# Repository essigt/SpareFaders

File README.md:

# SpareFaders

A (still work in progress) STM32-BluePill based MA-Style midi controller featuring 60 buttons and 15 faders.

## PCB

The project is made up of two PCB types. A controller PCB and a keys PCB with can be assambled both for the keys above or under the faders.

### Assembly

## Front Plate

The files for the front plate will be uploaded soon.

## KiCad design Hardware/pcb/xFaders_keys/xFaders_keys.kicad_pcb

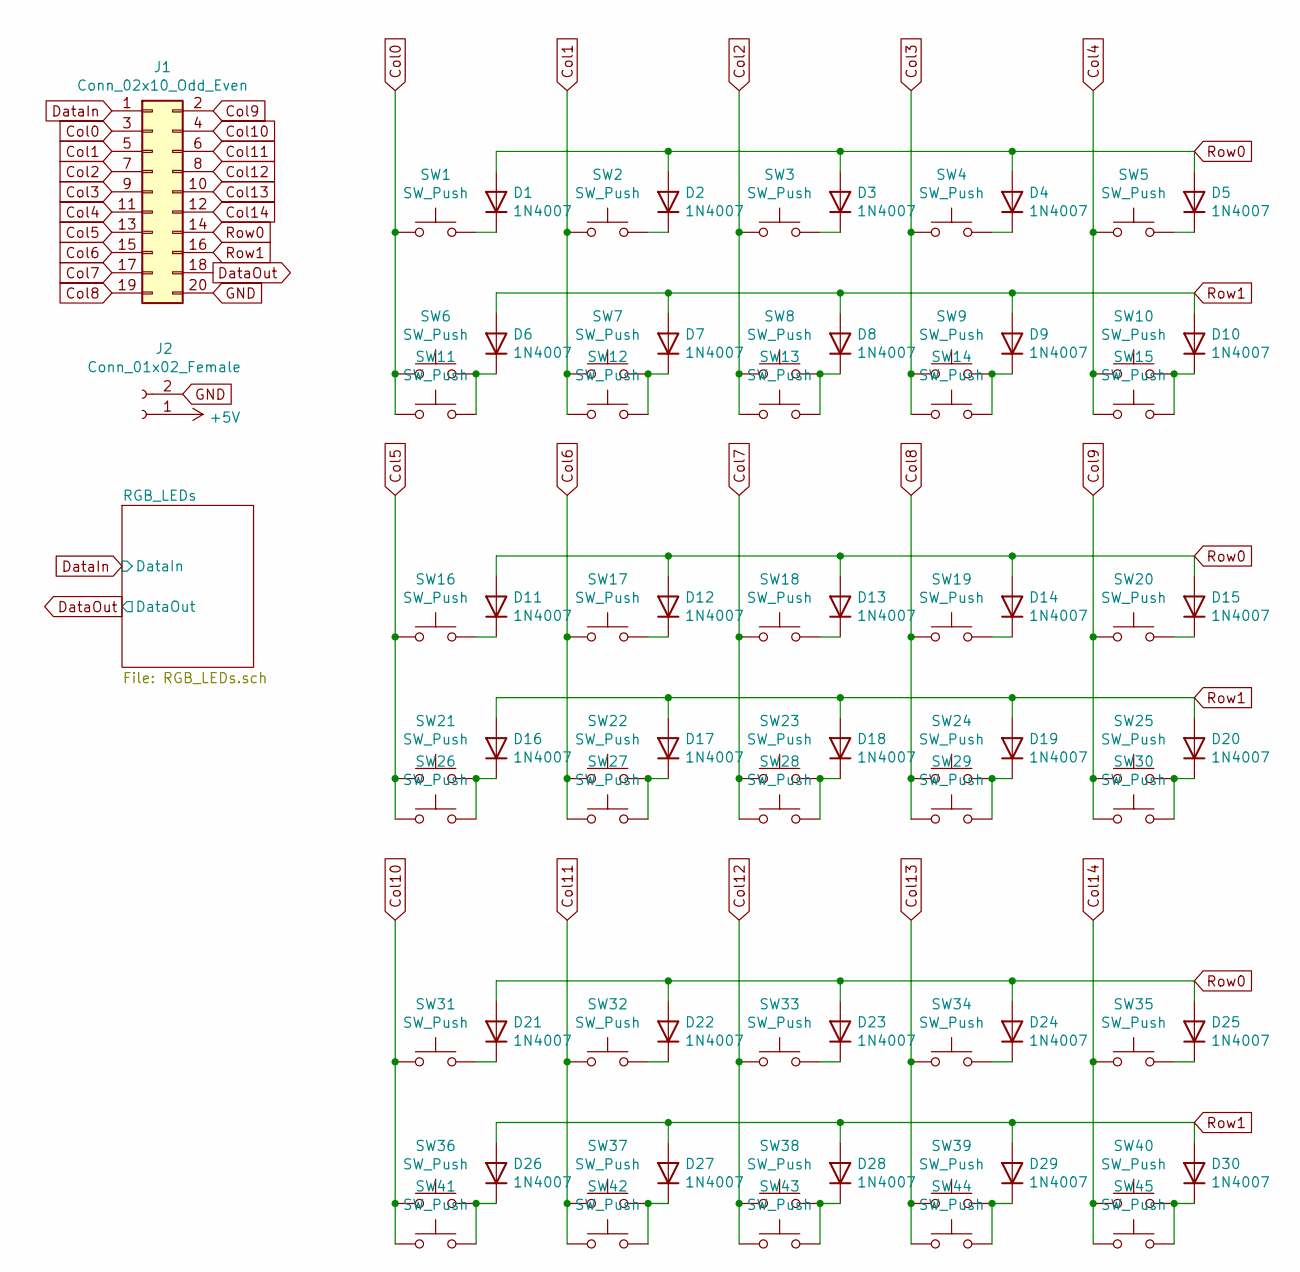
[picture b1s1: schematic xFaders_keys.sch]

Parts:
D1, D2, D3, D4, D5, D6, D7, D8, D9, D10, D11, D12, D13, D14, D15, D16, D17, D18, D19, D20, D21, D22, D23, D24, D25, D26, D27, D28, D29, D30: 1N4007; D_DO-35_SOD27_P10.16mm_Horizontal
J1: Conn_02x10_Odd_Even; PinHeader_2x10_P2.54mm_Vertical
J2: Conn_01x02_Female; PinHeader_1x02_P2.54mm_Vertical
SW1, SW2, SW3, SW4, SW5, SW6, SW7, SW8, SW9, SW10, SW11, SW12, SW13, SW14, SW15, SW16, SW17, SW18, SW19, SW20, SW21, SW22, SW23, SW24, SW25, SW26, SW27, SW28, SW29, SW30, SW31, SW32, SW33, SW34, SW35, SW36, SW37, SW38, SW39, SW40, SW41, SW42, SW43, SW44, SW45: SW_Push; SW_Cherry_MX_1.00u_PCB

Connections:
Col0: J1.3, SW1.1, SW6.1, SW11.1
Col1: J1.5, SW2.1, SW7.1, SW12.1
Col2: J1.7, SW3.1, SW8.1, SW13.1
Col3: J1.9, SW4.1, SW9.1, SW14.1
Col4: J1.11, SW5.1, SW10.1, SW15.1
Col5: J1.13, SW16.1, SW21.1, SW26.1
Col6: J1.15, SW17.1, SW22.1, SW27.1
Col7: J1.17, SW18.1, SW23.1, SW28.1
Col8: J1.19, SW19.1, SW24.1, SW29.1
Col9: J1.2, SW20.1, SW25.1, SW30.1
Col10: J1.4, SW31.1, SW36.1, SW41.1
Col11: J1.6, SW32.1, SW37.1, SW42.1
Col12: J1.8, SW33.1, SW38.1, SW43.1
Col13: J1.10, SW34.1, SW39.1, SW44.1
Col14: J1.12, SW35.1, SW40.1, SW45.1
DataIn: J1.1; also elsewhere on the board
DataOut: J1.18; also elsewhere on the board
unnamed: D1.1 (K), SW1.2
unnamed: D2.1 (K), SW2.2
unnamed: D3.1 (K), SW3.2
unnamed: D4.1 (K), SW4.2
unnamed: D5.1 (K), SW5.2
unnamed: D6.1 (K), SW6.2, SW11.2
unnamed: D7.1 (K), SW7.2, SW12.2
unnamed: D8.1 (K), SW8.2, SW13.2
unnamed: D9.1 (K), SW9.2, SW14.2
unnamed: D10.1 (K), SW10.2, SW15.2
unnamed: D11.1 (K), SW16.2
unnamed: D12.1 (K), SW17.2
unnamed: D13.1 (K), SW18.2
unnamed: D14.1 (K), SW19.2
unnamed: D15.1 (K), SW20.2
unnamed: D16.1 (K), SW21.2, SW26.2
unnamed: D17.1 (K), SW22.2, SW27.2
unnamed: D18.1 (K), SW23.2, SW28.2
unnamed: D19.1 (K), SW24.2, SW29.2
unnamed: D20.1 (K), SW25.2, SW30.2
unnamed: D21.1 (K), SW31.2
unnamed: D22.1 (K), SW32.2
unnamed: D23.1 (K), SW33.2
unnamed: D24.1 (K), SW34.2
unnamed: D25.1 (K), SW35.2
unnamed: D26.1 (K), SW36.2, SW41.2
unnamed: D27.1 (K), SW37.2, SW42.2
unnamed: D28.1 (K), SW38.2, SW43.2
unnamed: D29.1 (K), SW39.2, SW44.2
unnamed: D30.1 (K), SW40.2, SW45.2
Row0: D1.2 (A), D2.2 (A), D3.2 (A), D4.2 (A), D5.2 (A), D11.2 (A), D12.2 (A), D13.2 (A), D14.2 (A), D15.2 (A), D21.2 (A), D22.2 (A), D23.2 (A), D24.2 (A), D25.2 (A), J1.14
Row1: D6.2 (A), D7.2 (A), D8.2 (A), D9.2 (A), D10.2 (A), D16.2 (A), D17.2 (A), D18.2 (A), D19.2 (A), D20.2 (A), D26.2 (A), D27.2 (A), D28.2 (A), D29.2 (A), D30.2 (A), J1.16

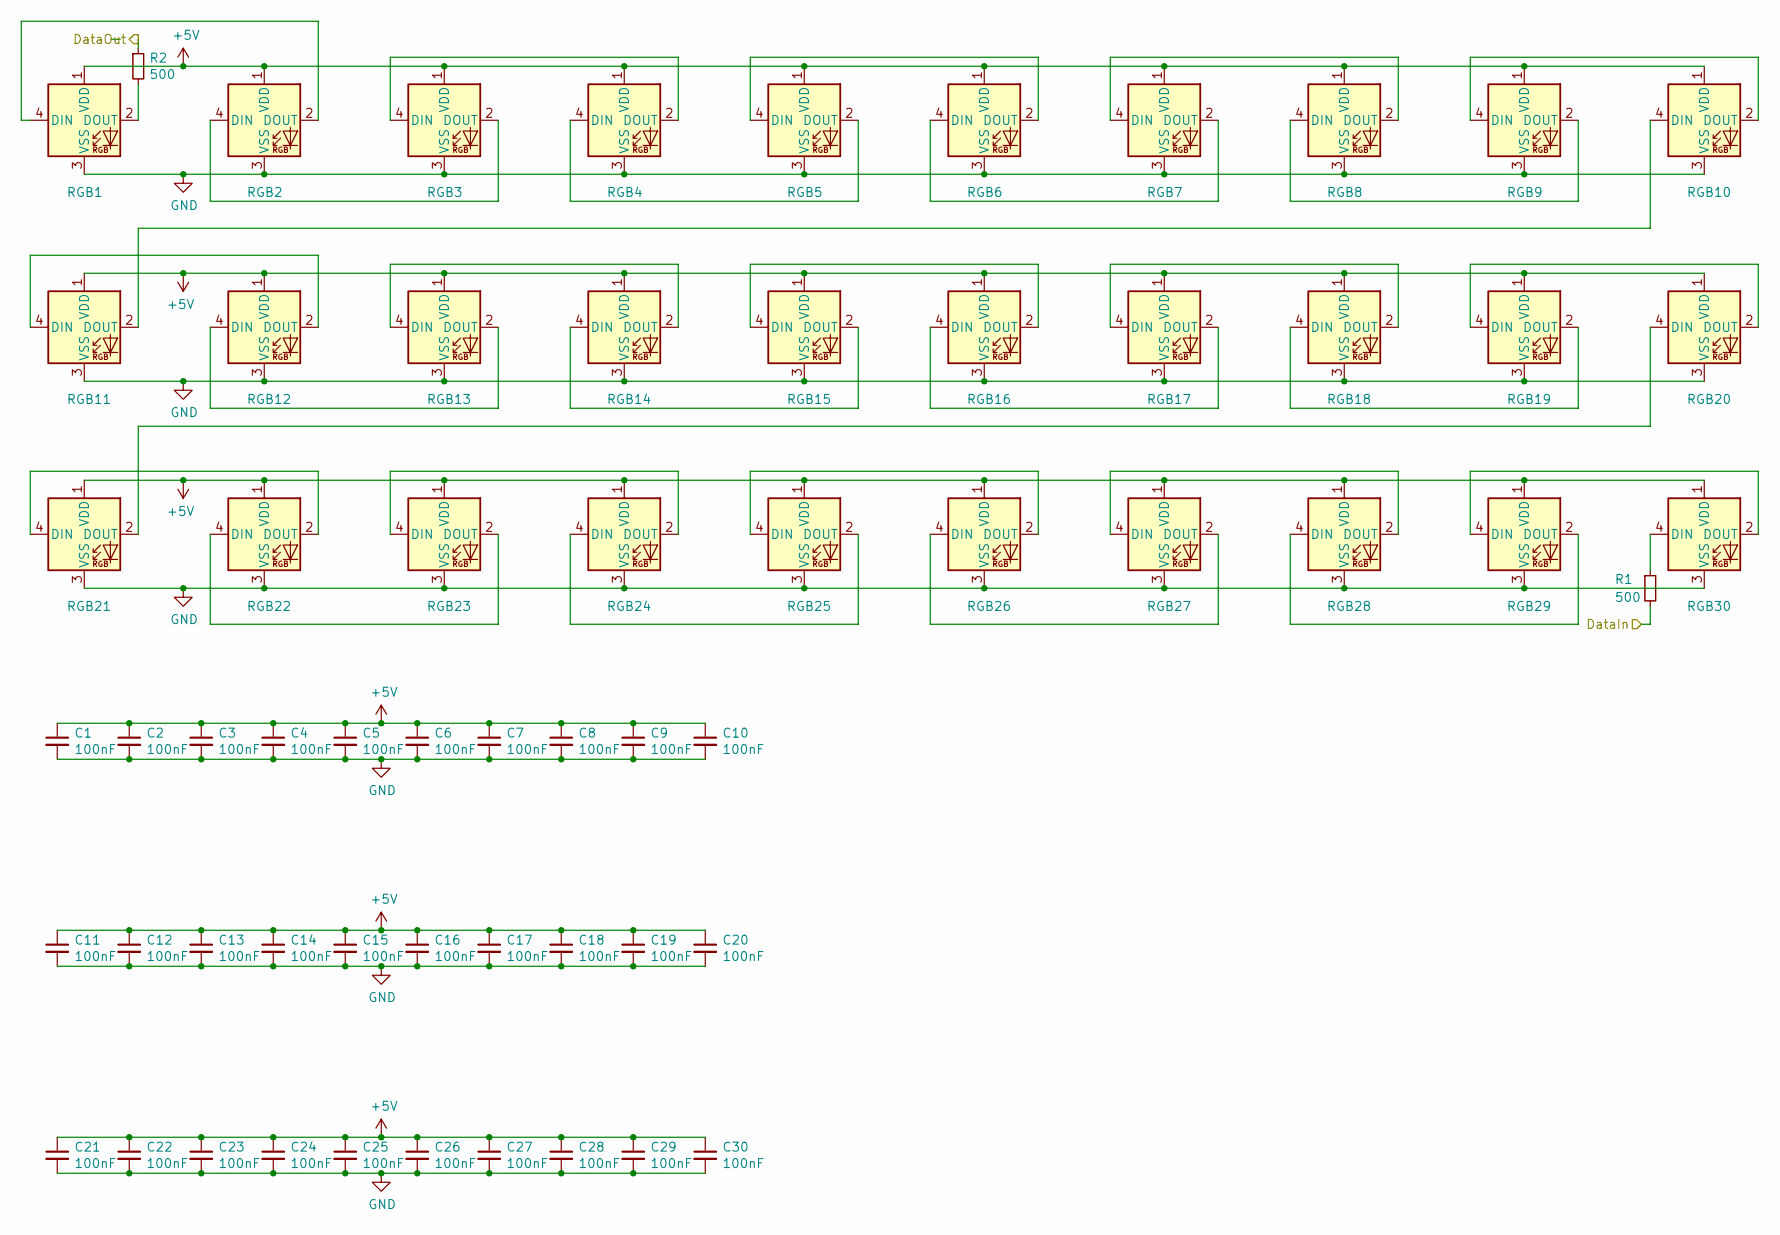
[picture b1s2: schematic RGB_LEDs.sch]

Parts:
C1, C2, C3, C4, C5, C6, C7, C8, C9, C10, C11, C12, C13, C14, C15, C16, C17, C18, C19, C20, C21, C22, C23, C24, C25, C26, C27, C28, C29, C30: 100nF; C_0603_1608Metric_Pad1.05x0.95mm_HandSolder
R1, R2: 500; R_Axial_DIN0204_L3.6mm_D1.6mm_P5.08mm_Horizontal
RGB1, RGB2, RGB3, RGB4, RGB5, RGB6, RGB7, RGB8, RGB9, RGB10, RGB11, RGB12, RGB13, RGB14, RGB15, RGB16, RGB17, RGB18, RGB19, RGB20, RGB21, RGB22, RGB23, RGB24, RGB25, RGB26, RGB27, RGB28, RGB29, RGB30: SK6812MINI-E; MX_SK6812MINI-E

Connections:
DataIn: R1.2; also elsewhere on the board
DataOut: R2.1; also elsewhere on the board
unnamed: R1.1, RGB30.4 (DIN)
unnamed: R2.2, RGB1.2 (DOUT)
unnamed: RGB1.4 (DIN), RGB2.2 (DOUT)
unnamed: RGB2.4 (DIN), RGB3.2 (DOUT)
unnamed: RGB3.4 (DIN), RGB4.2 (DOUT)
unnamed: RGB4.4 (DIN), RGB5.2 (DOUT)
unnamed: RGB5.4 (DIN), RGB6.2 (DOUT)
unnamed: RGB6.4 (DIN), RGB7.2 (DOUT)
unnamed: RGB7.4 (DIN), RGB8.2 (DOUT)
unnamed: RGB8.4 (DIN), RGB9.2 (DOUT)
unnamed: RGB9.4 (DIN), RGB10.2 (DOUT)
unnamed: RGB10.4 (DIN), RGB11.2 (DOUT)
unnamed: RGB11.4 (DIN), RGB12.2 (DOUT)
unnamed: RGB12.4 (DIN), RGB13.2 (DOUT)
unnamed: RGB13.4 (DIN), RGB14.2 (DOUT)
unnamed: RGB14.4 (DIN), RGB15.2 (DOUT)
unnamed: RGB15.4 (DIN), RGB16.2 (DOUT)
unnamed: RGB16.4 (DIN), RGB17.2 (DOUT)
unnamed: RGB17.4 (DIN), RGB18.2 (DOUT)
unnamed: RGB18.4 (DIN), RGB19.2 (DOUT)
unnamed: RGB19.4 (DIN), RGB20.2 (DOUT)
unnamed: RGB20.4 (DIN), RGB21.2 (DOUT)
unnamed: RGB21.4 (DIN), RGB22.2 (DOUT)
unnamed: RGB22.4 (DIN), RGB23.2 (DOUT)
unnamed: RGB23.4 (DIN), RGB24.2 (DOUT)
unnamed: RGB24.4 (DIN), RGB25.2 (DOUT)
unnamed: RGB25.4 (DIN), RGB26.2 (DOUT)
unnamed: RGB26.4 (DIN), RGB27.2 (DOUT)
unnamed: RGB27.4 (DIN), RGB28.2 (DOUT)
unnamed: RGB28.4 (DIN), RGB29.2 (DOUT)
unnamed: RGB29.4 (DIN), RGB30.2 (DOUT)

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
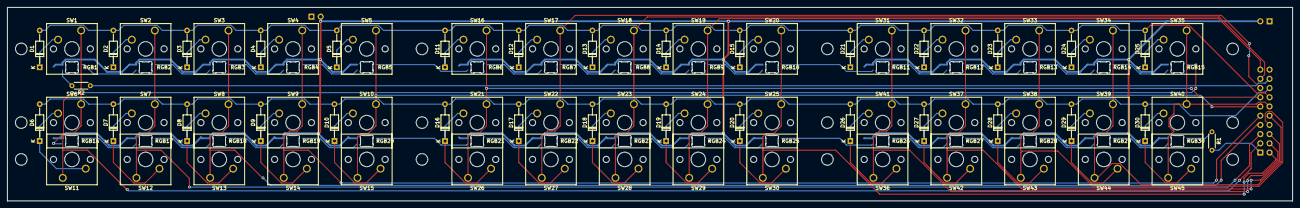
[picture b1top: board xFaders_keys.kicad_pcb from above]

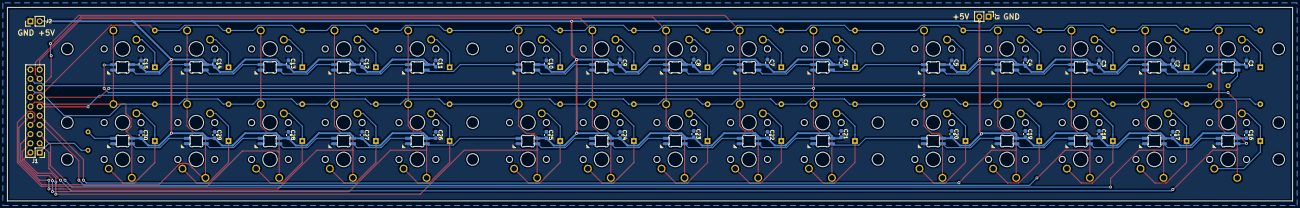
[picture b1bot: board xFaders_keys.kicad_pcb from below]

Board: 2 copper layers, 354.3 x 53.3 mm, 140 parts (33 on the bottom side), 82 nets.

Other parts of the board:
J3: Conn_01x02_Female; PinHeader_1x02_P2.54mm_Vertical

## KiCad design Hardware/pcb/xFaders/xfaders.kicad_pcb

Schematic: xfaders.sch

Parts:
C1, C2: 10 uF; C_Disc_D5.0mm_W2.5mm_P5.00mm
J1, J2, J3, J4, J5, J6, J7, J8, J9, J10, J11, J12, J13, J14, J15: Conn_01x03_Male; FanPinHeader_1x03_P2.54mm_Vertical
J16, J17, J18: Conn_02x10_Odd_Even; PinHeader_2x10_P2.54mm_Vertical
J19: PWR In; PinHeader_1x02_P2.54mm_Vertical
J20, J21, J22: 5V; PinHeader_1x02_P2.54mm_Vertical
Q1: 2N7000; TO-92_Inline
R1, R2, R3, R4, R5, R6: R; R_Axial_DIN0207_L6.3mm_D2.5mm_P7.62mm_Horizontal
R7, R8: 10k; R_Axial_DIN0207_L6.3mm_D2.5mm_P7.62mm_Horizontal
U1, U3: 4051; DIP-16_W7.62mm_Socket
U2: BluePill_STM32F103C
U4: LM1084-5.0; TO-220-3_Vertical

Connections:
Col0: J16.3, J17.3, J18.3, U2.13
Col1: J16.5, J17.5, J18.5, U2.14
Col2: J16.7, J17.7, J18.7, U2.15
Col3: J16.9, J17.9, J18.9, U2.16
Col4: J16.11, J17.11, J18.11, U2.4
Col5: J16.13, J17.13, J18.13, U2.3
Col6: J16.15, J17.15, J18.15, U2.37
Col7: J16.17, J17.17, J18.17, U2.36
Col8: J16.19, J17.19, J18.19, U2.35
Col9: J16.2, J17.2, J18.2, U2.34
Col10: J16.4, J17.4, J18.4, U2.33
Col11: J16.6, J17.6, J18.6, U2.32
Col12: J16.8, J17.8, J18.8, U2.31
Col13: J16.10, J17.10, J18.10, U2.30
Col14: J16.12, J17.12, J18.12, U2.25
GND: C1.2, C2.2, J1.1, J2.1, J3.1, J4.1, J5.1, J6.1, J7.1, J8.1, J9.1, J10.1, J11.1, J12.1, J13.1, J14.1, J15.1, J16.20, J17.20, J18.20, J19.1, J20.1, J21.1, J22.1, U1.6 (~E), U1.7 (VEE), U1.8 (Vss), U2.19, U2.20, U2.39, U3.6 (~E), U3.7 (VEE), U3.8 (Vss), U4.1
unnamed: C1.1, J19.2, U4.3
unnamed: J1.2, U3.13 (X0)
unnamed: J2.2, U3.14 (X1)
unnamed: J3.2, U3.15 (X2)
unnamed: J4.2, U3.12 (X3)
unnamed: J5.2, U3.1 (X4)
unnamed: J6.2, U3.5 (X5)
unnamed: J7.2, U3.2 (X6)
unnamed: J8.2, U3.4 (X7)
unnamed: J9.2, U1.15 (X2)
unnamed: J10.2, U1.14 (X1)
unnamed: J11.2, U1.13 (X0)
unnamed: J12.2, U1.12 (X3)
unnamed: J13.2, U1.1 (X4)
unnamed: J14.2, U1.5 (X5)
unnamed: J15.2, U1.2 (X6)
unnamed: J16.18, J17.1
unnamed: J17.18, J18.1
unnamed: U1.3 (X), U2.5
unnamed: U1.9 (C), U2.23, U3.9 (C)
unnamed: U1.10 (B), U2.27, U3.10 (B)
unnamed: U1.11 (A), U2.21, U3.11 (A)
unnamed: U2.6, U3.3 (X)
Row0: J16.14, R1.2, U2.7
Row1: J16.16, R2.2, U2.8
Row2: J17.14, R3.2, U2.9
Row3: J17.16, R4.2, U2.10
Row4: J18.14, R5.2, U2.11
Row5: J18.16, R6.2, U2.12
SPI_3V3: Q1.1, R7.2, U2.24
SPI_5V: J16.1, Q1.3, R8.2
VCC3V3: J1.3, J2.3, J3.3, J4.3, J5.3, J6.3, J7.3, J8.3, J9.3, J10.3, J11.3, J12.3, J13.3, J14.3, J15.3, Q1.2, R1.1, R2.1, R3.1, R4.1, R5.1, R6.1, R7.1, U1.16 (Vdd), U2.18, U2.40, U3.16 (Vdd)
VCC5V: C2.1, J20.2, J21.2, J22.2, R8.1, U4.2

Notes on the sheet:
SPI step-up converter
5V 5A power supply
see: http://electronictoofree.blogspot.com/2018/04/reading-schematic-sparkfun.html

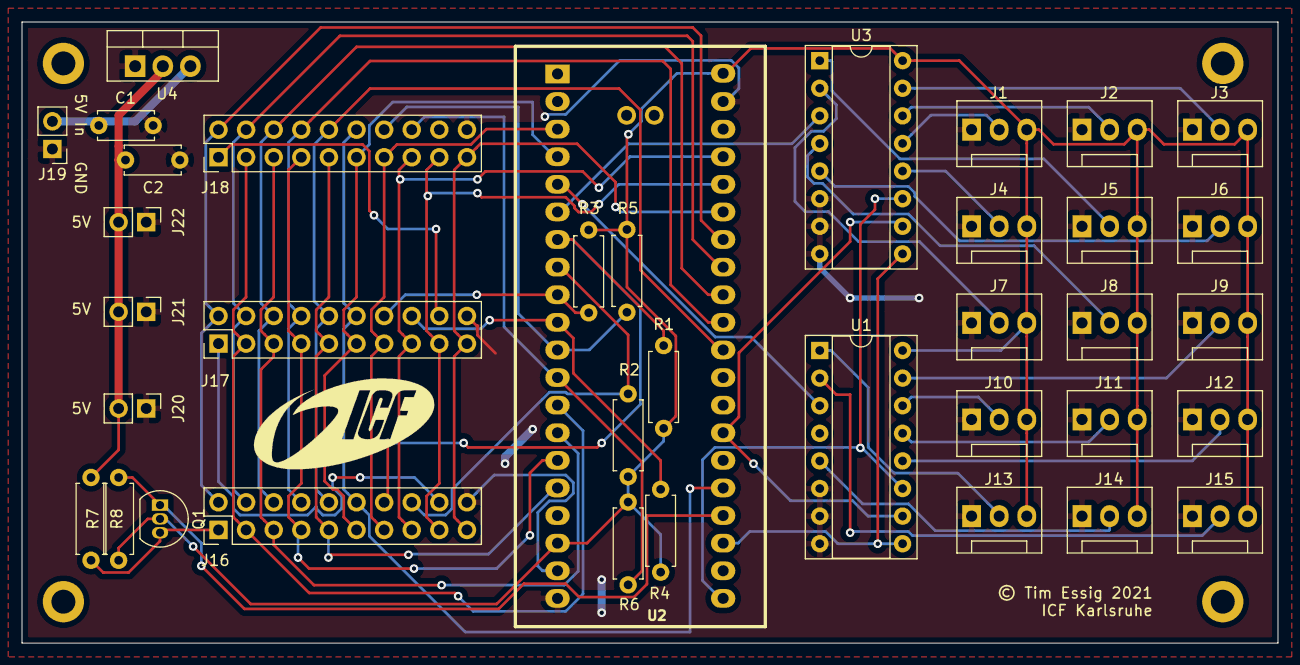
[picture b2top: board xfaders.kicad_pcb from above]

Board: 2 copper layers, 115.6 x 57.1 mm, 37 parts (0 on the bottom side), 49 nets.

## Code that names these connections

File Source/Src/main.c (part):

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	WRITE_REG(GPIOB->BSRR, GPIO_BSRR_BS8); //COL 7   High
	WRITE_REG(GPIOB->BSRR, GPIO_BSRR_BS7); //COL 8   High
	WRITE_REG(GPIOB->BSRR, GPIO_BSRR_BS6);  //COL 9   High
	WRITE_REG(GPIOB->BSRR, GPIO_BSRR_BS5);  //COL10   High
	WRITE_REG(GPIOB->BSRR, GPIO_BSRR_BS4);  //COL11   High
	WRITE_REG(GPIOB->BSRR, GPIO_BSRR_BS3);  //COL12   High
	WRITE_REG(GPIOA->BSRR, GPIO_BSRR_BS15);  //COL13   High
	WRITE_REG(GPIOA->BSRR, GPIO_BSRR_BS8);  //COL14   High
}

void setCol(uint8_t col) {
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	}

	if(col == 11) {
		WRITE_REG(GPIOB->BSRR, GPIO_BSRR_BR4);  //COL11
	}

	if(col == 12) {
		WRITE_REG(GPIOB->BSRR, GPIO_BSRR_BR3);  //COL12
	}

	if(col == 13) {
		WRITE_REG(GPIOA->BSRR, GPIO_BSRR_BR15);  //COL13
	}

	if(col == 14) {
		WRITE_REG(GPIOA->BSRR, GPIO_BSRR_BR8);  //COL14
	}
}

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
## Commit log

2020-03-05 Initial commit / CubeMX Files / C Sources
2020-03-05 Add KiCad files
2020-03-05 Add images for documentation
2020-03-08 add frontplate CAD files
2020-06-11 Use us delay instead of ms delay to archive much higher update rate
2021-02-11 Add kicad library for SK6812 MINI-E RGB LEDs
2021-02-12 Rotate keys in bottom row to make room for leds
2021-02-19 Add RGB LEDs and capacitors to Schema and PCB
2021-04-10 Update PCB for new RGB LEDs and 5V power supply
2021-04-10 Add gerber files for version 2.0
2021-07-11 Add output of RGB data via SPI
2021-07-11 Add basic USB-MIDI receive functionality
2021-07-16 Rename USB Class files and types from HID to MIDI
2021-07-16 Apply led colors received over midi
2021-08-23 Add startup animation to leds
2021-08-23 FIX: Flickerin LEDs
    Quickfix: Disable IRQs while SPI Transmit
2021-08-23 FIX: Use PA10 instead of PB13 PIN for AD Multiplexer
2023-01-04 FIX: Bug in in button press detection, debounce faders
2023-01-04 Add run config
2024-01-05 Add interactive bom
2024-01-12 fix: improve adc timing to avoid interferences between faders
2024-01-12 fix: avoid faders not reaching its zero point because of hardware tolerances
2024-01-12 fix: low budget fix for faders not reaching its upper limit because of hardware tolerances
2024-01-12 fix: avoid fader getting stuck at value 1 instead of reaching 0

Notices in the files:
Source/Src/main.c:
© Copyright (c) 2019 STMicroelectronics.
All rights reserved.
This software component is licensed by ST under Ultimate Liberty license
(C) COPYRIGHT STMicroelectronics *****END OF FILE
Hardware/pcb/xFaders/xfaders.kicad_pcb:
© Tim Essig 2021
